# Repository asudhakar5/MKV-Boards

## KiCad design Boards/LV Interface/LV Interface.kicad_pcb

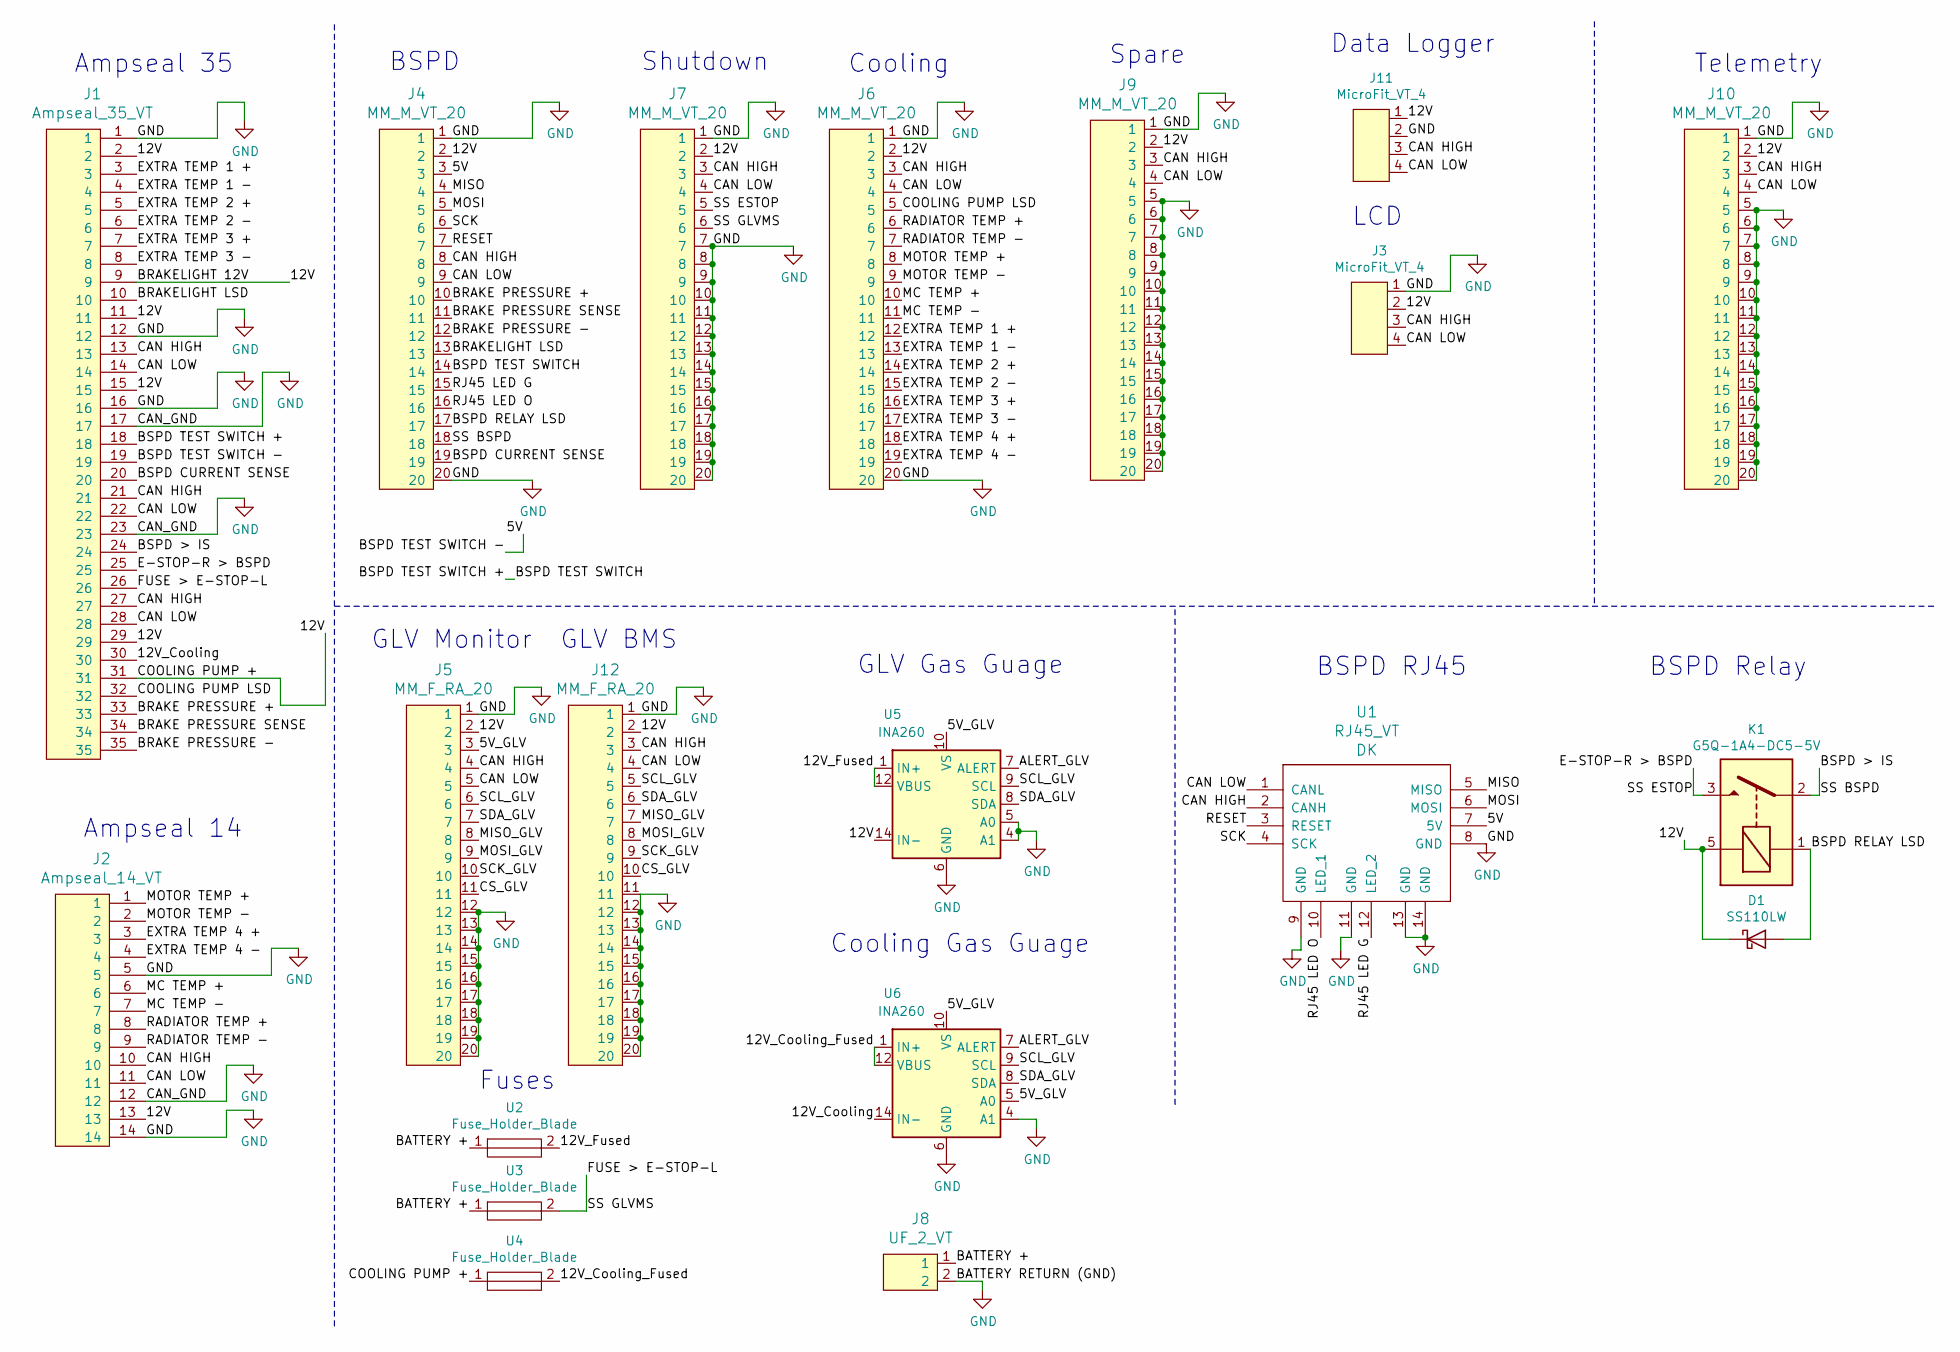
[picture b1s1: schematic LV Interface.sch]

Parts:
D1: SS110LW; D_SOD-123W_OEM; MPN SS110LWRVGCT-ND
J1: Ampseal_35_VT; Ampseal_35; MPN 1-776231-1
J2: Ampseal_14_VT; Ampseal_14; MPN 1-776261-1
J3, J11: MicroFit_VT_4
J4, J6, J7, J9, J10: MM_M_VT_20; micromatch_female_ra_20; MPN 2-215464-0
J5, J12: MM_F_RA_20; micromatch_female_ra_20; MPN 2-338070-0
J8: UF_2_VT; Ultrafit_2; MPN WM11570-ND
K1: G5Q-1A4-DC5-5V; Relay_SPST_OMRON-G5Q-1A4_OEM; MPN Z3632-ND
U1: RJ45_VT; RJ45-Vertical; MPN MRJ-5481-01-ND
U2, U3, U4: Fuse_Holder_Blade; Fuse_Block_Holder
U5, U6: INA260; TSSOP-16_4.4x5mm_P0.65mm

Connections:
/5V: J1.19, J4.3, U1.7 (5V)
/5V_GLV: J5.3, U5.10 (VS), U6.5 (A0), U6.10 (VS)
/12V: D1.1 (K), J1.2, J1.9, J1.11, J1.15, J1.29, J1.31, J2.13, J3.2, J4.2, J5.2, J6.2, J7.2, J9.2, J10.2, J11.1, J12.2, K1.5, U4.1, U5.14 (IN-), U5.15 (IN-), U5.16 (IN-)
/12V_Cooling: J1.30, U6.14 (IN-), U6.15 (IN-), U6.16 (IN-)
/12V_Cooling_Fused: U4.2, U6.1 (IN+), U6.2 (IN+), U6.3 (IN+), U6.12 (VBUS)
/12V_Fused: U2.2, U5.1 (IN+), U5.2 (IN+), U5.3 (IN+), U5.12 (VBUS)
/ALERT_GLV: U5.7 (ALERT), U6.7 (ALERT)
/BATTERY +: J8.1, U2.1, U3.1
/BRAKE PRESSURE +: J1.33, J4.10
/BRAKE PRESSURE -: J1.35, J4.12
/BRAKE PRESSURE SENSE: J1.34, J4.11
/BRAKELIGHT LSD: J1.10, J4.13
/BSPD > IS: J1.24, J4.18, K1.2
/BSPD CURRENT SENSE: J1.20, J4.19
/BSPD RELAY LSD: D1.2 (A), J4.17, K1.1
/BSPD TEST SWITCH: J1.18, J4.14
/CAN HIGH: J1.13, J1.21, J1.27, J2.10, J3.3, J4.8, J5.4, J6.3, J7.3, J9.3, J10.3, J11.3, J12.3, U1.2 (CANH)
/CAN LOW: J1.14, J1.22, J1.28, J2.11, J3.4, J4.9, J5.5, J6.4, J7.4, J9.4, J10.4, J11.4, J12.4, U1.1 (CANL)
/COOLING PUMP LSD: J1.32, J6.5
/CS_GLV: J5.11, J12.10
/E-STOP-R > BSPD: J1.25, J7.5, K1.3
/EXTRA TEMP 1 +: J1.3, J6.12
/EXTRA TEMP 1 -: J1.4, J6.13
/EXTRA TEMP 2 +: J1.5, J6.14
/EXTRA TEMP 2 -: J1.6, J6.15
/EXTRA TEMP 3 +: J1.7, J6.16
/EXTRA TEMP 3 -: J1.8, J6.17
/EXTRA TEMP 4 +: J2.3, J6.18
/EXTRA TEMP 4 -: J2.4, J6.19
/FUSE > E-STOP-L: J1.26, J7.6, U3.2
/MC TEMP +: J2.6, J6.10
/MC TEMP -: J2.7, J6.11
/MISO: J4.4, U1.5 (MISO)
/MISO_GLV: J5.8, J12.7
/MOSI: J4.5, U1.6 (MOSI)
/MOSI_GLV: J5.9, J12.8
/MOTOR TEMP +: J2.1, J6.8
/MOTOR TEMP -: J2.2, J6.9
/RADIATOR TEMP +: J2.8, J6.6
/RADIATOR TEMP -: J2.9, J6.7
/RESET: J4.7, U1.3 (RESET)
/RJ45 LED G: J4.15, U1.12 (LED_2)
/RJ45 LED O: J4.16, U1.10 (LED_1)
/SCK: J4.6, U1.4 (SCK)
/SCK_GLV: J5.10, J12.9
/SCL_GLV: J5.6, J12.5, U5.9 (SCL), U6.9 (SCL)
/SDA_GLV: J5.7, J12.6, U5.8 (SDA), U6.8 (SDA)
GND: J1.1, J1.12, J1.16, J1.17, J1.23, J2.5, J2.12, J2.14, J3.1, J4.1, J4.20, J5.1, J5.12, J5.13, J5.14, J5.15, J5.16, J5.17, J5.18, J5.19, J5.20, J6.1, J6.20, J7.1, J7.7, J7.8, J7.9, J7.10, J7.11, J7.12, J7.13, J7.14, J7.15, J7.16, J7.17, J7.18, J7.19, J7.20, J8.2, J9.1, J9.5, J9.6, J9.7, J9.8, J9.9, J9.10, J9.11, J9.12, J9.13, J9.14, J9.15, J9.16, J9.17, J9.18, J9.19, J9.20, J10.1, J10.5, J10.6, J10.7, J10.8, J10.9, J10.10, J10.11, J10.12, J10.13, J10.14, J10.15, J10.16, J10.17, J10.18, J10.19, J10.20, J11.2, J12.1, J12.11, J12.12, J12.13, J12.14, J12.15, J12.16, J12.17, J12.18, J12.19, J12.20, U1.8 (GND), U1.9 (GND), U1.11 (GND), U1.13 (GND), U1.14 (GND), U5.4 (A1), U5.5 (A0), U5.6 (GND), U5.11 (GND), U6.4 (A1), U6.6 (GND), U6.11 (GND)

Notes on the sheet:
Ampseal 35
Ampseal 14
BSPD
Shutdown
Cooling
Spare
Telemetry
LCD
GLV Monitor
GLV BMS
BSPD Relay
Fuses
BSPD RJ45
Data Logger
Cooling Gas Guage
GLV Gas Guage

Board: 4 copper layers, 20 parts (2 on the bottom side), 48 nets, no tracks yet.

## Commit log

2019-12-13 Saving Changes
2019-12-13 First Layout Changes
2019-12-13 Saving Ampeseal orientations
2019-12-13 Saving work
